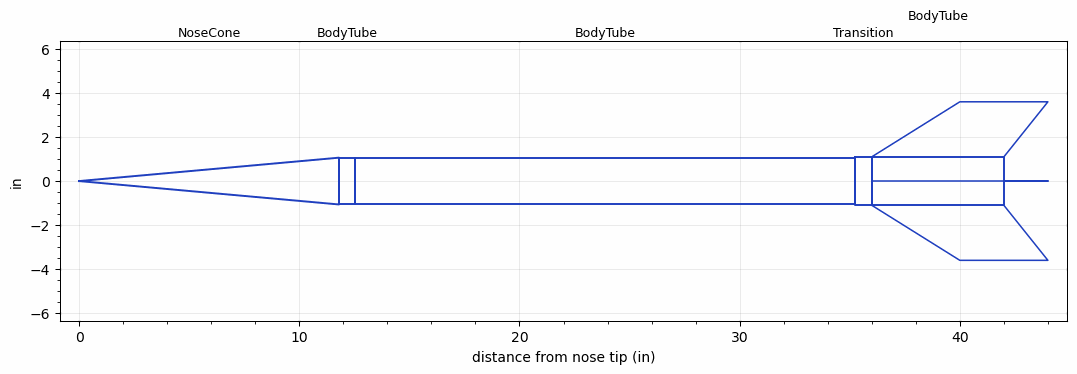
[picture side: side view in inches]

<RASAeroDocument>
 <FileVersion>2</FileVersion>
 <RocketDesign>
  <NoseCone>
   <Length>11.8</Length>
   <Diameter>2.125</Diameter>
   <Shape>Conical</Shape>
   <BluntRadius>0.065</BluntRadius>
   <Location>0</Location>
  </NoseCone>
  <BodyTube>
   <Length>0.75</Length>
   <Diameter>2.125</Diameter>
   <Location>11.8</Location>
  </BodyTube>
  <BodyTube>
   <Length>22.7</Length>
   <Diameter>2.125</Diameter>
   <Location>12.55</Location>
  </BodyTube>
  <Transition>
   <Length>0.75</Length>
   <Diameter>2.2</Diameter>
   <Location>35.25</Location>
   <RearDiameter>2.2</RearDiameter>
  </Transition>
  <BodyTube>
   <Length>6</Length>
   <Diameter>2.2</Diameter>
   <Location>36</Location>
   <Fin>
    <Count>4</Count>
    <Chord>6</Chord>
    <Span>2.5</Span>
    <SweepDistance>4</SweepDistance>
    <TipChord>4</TipChord>
    <Thickness>0.1578</Thickness>
    <LERadius>0.01</LERadius>
    <Location>6</Location>
    <AirfoilSection>Hexagonal Blunt Base</AirfoilSection>
    <FX1>0.5</FX1>
   </Fin>
  </BodyTube>
  <Surface>Smooth Paint</Surface>
  <ModifiedBarrowman>True</ModifiedBarrowman>
  <Turbulence>True</Turbulence>
  <UseBooster1>False</UseBooster1>
  <UseBooster2>False</UseBooster2>
 </RocketDesign>
 <LaunchSite>
  <Altitude>2000</Altitude>
  <Pressure>29.92</Pressure>
  <RodAngle>0</RodAngle>
  <RodLength>7</RodLength>
  <Temperature>59</Temperature>
  <WindSpeed>4.47</WindSpeed>
 </LaunchSite>
 <Recovery>
  <Altitude1>0</Altitude1>
  <Altitude2>0</Altitude2>
  <DeviceType1>None</DeviceType1>
  <DeviceType2>None</DeviceType2>
  <Event1>False</Event1>
  <Event2>False</Event2>
  <Size1>0</Size1>
  <Size2>0</Size2>
  <EventType1>None</EventType1>
  <EventType2>None</EventType2>
  <CD1>0</CD1>
  <CD2>0</CD2>
 </Recovery>
 <SimulationList>
  <Simulation>
   <SustainerEngine>L2587AB  (Alex)</SustainerEngine>
   <SustainerLaunchWt>8.15</SustainerLaunchWt>
   <SustainerNozzleDiameter>1.9</SustainerNozzleDiameter>
   <SustainerCG>28</SustainerCG>
   <SustainerIgnitionDelay>0</SustainerIgnitionDelay>
   <Booster1SeparationDelay>0</Booster1SeparationDelay>
   <Booster1IgnitionDelay>0</Booster1IgnitionDelay>
   <IncludeBooster1>False</IncludeBooster1>
   <Booster2Delay>0</Booster2Delay>
   <IncludeBooster2>False</IncludeBooster2>
   <TimetoApogee>27.59054</TimetoApogee>
   <MaxAltitude>22127.14</MaxAltitude>
   <MaxVelocity>3844.135</MaxVelocity>
   <OptimumWt>9.862499</OptimumWt>
   <OptimumMaxAlt>9.862499</OptimumMaxAlt>
  </Simulation>
 </SimulationList>
</RASAeroDocument>
